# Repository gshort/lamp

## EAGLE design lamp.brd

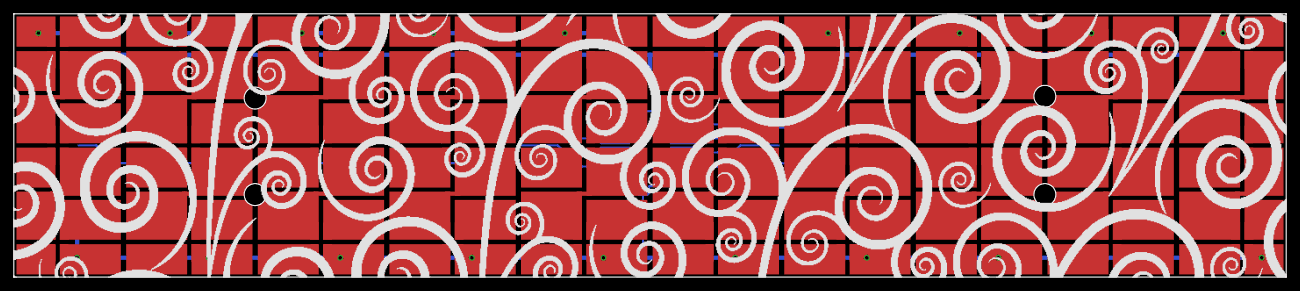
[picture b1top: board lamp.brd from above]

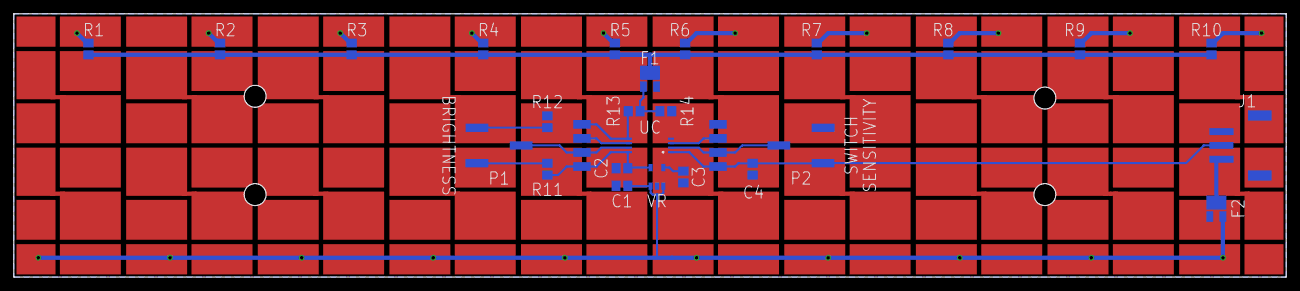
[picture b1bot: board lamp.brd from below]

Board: 2 copper layers, 184.2 x 38.1 mm, 63 parts (33 on the bottom side), 45 nets.

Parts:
C1: 1µF; 0805
C2: 2.2µF; 0805
C3: 10nF; 0805
C4: 100pF; 0805
F1: SI2318DS; SOT-23-3
F2: SI2319DS; SOT-23-3
GND: SMD1,27-2,54
P1: 10kΩ; 3361P
P2: 2MΩ; 3361P
PB0, PB1, PB2, PB3, PB4, PB5: SMD1,27-2,54
R1, R2, R3, R4, R5, R6, R7, R8, R9, R10: 36Ω; 0805
R11, R12: 0805
R13: 100Ω; 0805
R14: 100kΩ; 0805
U$1, U$2, U$3, U$4, U$5, U$6, U$7, U$8, U$9, U$10, U$11, U$12, U$13, U$14, U$15, U$16, U$17, U$18, U$19, U$20, U$21, U$22, U$23, U$24, U$25, U$26, U$27, U$28, U$29, U$30: CLA1BWKWMKW-4; PLCC4
U$32: HEADER-3X1; SM4
UC: ATTINY45; TSSOP-8
VCC: SMD1,27-2,54
VR: LP2985; SOT-23-5

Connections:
+5V: C2.1, R11.1, UC.P$8, VCC.1, VR.P$5
+12V: F2.P$3, U$32.P$1
GND: C1.2, C2.2, C3.2, C4.2, F1.S$2, F2.P$1, GND.1, R12.2, R14.1, U$32.P$3, UC.P$4, VR.P$2
unnamed: U$1.P$4, U$2.P$2
unnamed: R1.2, U$3.P$4
unnamed: U$2.P$4, U$3.P$2
unnamed: U$4.P$4, U$5.P$2
unnamed: R2.2, U$6.P$4
unnamed: U$5.P$4, U$6.P$2
unnamed: U$7.P$4, U$8.P$2
unnamed: R3.2, U$9.P$4
unnamed: U$8.P$4, U$9.P$2
unnamed: U$10.P$4, U$11.P$2
unnamed: R4.2, U$12.P$4
unnamed: U$11.P$4, U$12.P$2
unnamed: R6.2, U$18.P$4
unnamed: F1.P$1, R13.2, R14.2
unnamed: U$16.P$4, U$17.P$2
unnamed: P1.P$3, R11.2
unnamed: C4.1, P2.P$1, PB5.1, U$32.P$2, UC.P$1
unnamed: U$19.P$4, U$20.P$2
unnamed: R7.2, U$21.P$4
unnamed: U$20.P$4, U$21.P$2
unnamed: U$22.P$4, U$23.P$2
unnamed: R8.2, U$24.P$4
unnamed: U$23.P$4, U$24.P$2
unnamed: U$25.P$4, U$26.P$2
unnamed: R9.2, U$27.P$4
unnamed: U$26.P$4, U$27.P$2
unnamed: U$28.P$4, U$29.P$2
unnamed: R10.2, U$30.P$4
unnamed: U$29.P$4, U$30.P$2
unnamed: U$13.P$4, U$14.P$2
unnamed: U$14.P$4, U$15.P$2
unnamed: F1.P$3, R1.1, R2.1, R3.1, R4.1, R5.1, R6.1, R7.1, R8.1, R9.1, R10.1
unnamed: P1.P$1, R12.1
unnamed: P2.P$2, PB3.1, UC.P$2
unnamed: PB4.1, UC.P$3
unnamed: U$17.P$4, U$18.P$2
unnamed: R5.2, U$15.P$4
unnamed: C1.1, F2.S$2, U$1.P$2, U$4.P$2, U$7.P$2, U$10.P$2, U$13.P$2, U$16.P$2, U$19.P$2, U$22.P$2, U$25.P$2, U$28.P$2, VR.P$1, VR.P$3
unnamed: C3.1, VR.P$4
unnamed: PB0.1, R13.1, UC.P$5
unnamed: P1.P$2, PB2.1, UC.P$7
unnamed: PB1.1, UC.P$6

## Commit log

2014-02-21 Initial commit. Partial schematic, partial board.
2014-02-27 A bunch of layout and traces. Still need some support components for the microcontroller.
2014-02-27 Added power supply for microcontroller, more routing, and some minor rearrangement on parts. Added solder pads for controller. Added ground plane for bottom.
2014-02-27 Fixed a broken ground on the voltage regulator
2014-02-27 Finished top layer: added heat sink flags on the leds, filled in the ground plane, did some more routing. Because I'm on babby's first eagle license, I can't place the last 8 parts, but all the routi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
2014-02-28 Fiddled the board xml by hand to place the last few parts. Some more adjustment of traces. Added a low-noise cap to the 5v regulator.
2014-03-01 More fiddling: moved some parts around, started adding capacitive touch on/off switch
2014-03-01 Fixed some footprints, mangled some others, and added a temporary placeholder for the header block that will be for power and the switch.
2014-03-01 fixed led vsupply to be from the pfet added in last commit instead of straight from +12v
2014-03-03 Swapped pins around on attiny45 for a better layout, adjusted layout accordingly. Much cleaner now.
2014-03-03 A little more schematic fine-tuning and board arrangement. Nothing significant.
2014-03-04 Finished footprint for header block. Fiddled around switch and brightness circuits. Fine-tuned placements of several parts. Added labels for switch/brightness adjustment trimpots. I think this is pre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
2014-03-05 Widened the board to 7.25 inches and rearranged everything accordingly.
2014-03-08 More fine-tuning, I think? I, umm...don't remember. Certainly nothing major...
2014-03-16 Fixed footprint for trimpots. Removed transistor array and replaced with single n fet. Adjusted layout for new/modified parts. Increased font size for all board markings. Changed capacitive switch pi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
2014-03-17 Moved stuff around for a comfier layout.
2014-03-17 Altered LED footprint to have a more conservative solder mask (small holes)
2014-03-17 Shifted mounting holes towards board center a little
2014-03-17 Moved pfet f2 so it's not sitting on the back of an LED
2014-03-17 Pulled the supply rail for the LED banks onto the back of the board.
2014-03-17 Added fancy silk screen on front of board for Art Reasons.
2014-03-17 Redid graphics, modified LED footprint to remove orientation pip but slightly round pin #1 instead
2014-03-17 Added top layer silkscreen source bmp
2014-03-18 Fixed nfet that controls led channels. Added resistors to pwm control line. Adjusted nfet and pfet symbols.
2014-03-19 Removed soft-start RC from reverse polarity protection fet F2. Removed solder mask holes from led vias so they will get tented instead.
2014-04-02 Various changes, I forget. Probably mostly artsy-fartsy silkscreen stuff.
